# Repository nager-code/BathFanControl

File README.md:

# BathFanControl

**Feuchteabhängige Steuerung für einen Badlüfter.** Die Platine sitzt direkt im Lüfterkasten, misst die Luftfeuchte und schaltet den Lüfter nur so lange, wie das Lüften tatsächlich etwas bringt. Über WLAN lässt sie sich einstellen und aktualisieren.

> [!WARNING]
> **Stand V1.0: Planung abgeschlossen – noch nicht gebaut, nicht getestet.** Schaltplan und Platine sind in KiCad ohne Befund geprüft, es gibt aber noch kein gefertigtes Muster und noch keine Firmware. Siehe [Projektstand](doku/stand.md).

> [!CAUTION]
> **Netzspannung 230 V.** Die Schaltung führt Netzspannung und wird in einem Feuchtraum eingebaut. Betrieb nur im geschlossenen Gehäuse, Anschluss durch eine Elektrofachkraft. Mehr unter [Sicherheit](#sicherheit).

## Worum geht es?

Die alte Steuerung des Badlüfters lief teilweise acht Stunden am Stück, ohne dass die Feuchte sank. BathFanControl macht es besser:

- **Misst die Luftfeuchte** mit einem Sensirion SHT40 (mit Schutzmembran) direkt am Lüfter-Einlass.
- **Prüft den Fortschritt:** Sinkt die Feuchte beim Lüften nicht (z. B. weil die Außenluft selbst feucht ist), legt die Steuerung eine Pause ein, statt weiterzulaufen.
- **Erkennt Aktivität im Bad** über einen zweiten 230-V-Eingang vom Lichtschalter.
- **Ist über WLAN erreichbar** (ESP32-C3), z. B. für Home Assistant, Einstellungen und Updates.
- **Zeigt den Zustand** über eine RGB-LED im Gehäusedeckel.

Entwickelt für einen **KN2-UP-Unterputzlüfter** (Einrohr-Lüftungssystem, ca. 50 W). Andere Lüfter mit einem Schaltkanal bis zu dieser Leistung sollten ebenfalls passen, das ist aber nicht geprüft.

## Eckdaten

| | |
|---|---|
| Versorgung | 230 V AC, Netzteil Hi-Link HLK-PM03 (3,3 V, 1 A) |
| Eingänge | Lichtschalter (230 V, galvanisch getrennt über Optokoppler) |
| Ausgang | Lüfter, geschaltet über Optotriac und Triac (Phase) |
| Sensor | Sensirion SHT40-AD1F-R2, Temperatur und relative Feuchte |
| Controller | Espressif ESP32-C3-MINI-1 (WLAN, USB eingebaut) |
| Anschluss | 4-polige Schraubklemme: L, Licht, N, Lüfter |
| Programmieren | USB-C auf der Platine (nur ohne Netzspannung), danach per WLAN |
| Platine | 68 x 72,5 mm, 2 Lagen, nur von oben bestückt, alle Teile bei JLCPCB lieferbar |
| Gehäuse | 72,6 x 77,1 x 25,7 mm, 3D-Druck |
| Entwurfswerkzeuge | KiCad 10, OpenSCAD |

## Bilder

| Lageplan der Bauteile | Gehäuse geschlossen und offen |
|---|---|
|  |  |

Weitere Ansichten: [Platine von allen Seiten](doku/platine_3d_ansichten.png), [Einbaulage im Lüfterkasten](doku/einbaulage.svg), [3D-Modell zum Drehen](doku/platine_3d.glb) (glTF), [Schaltplan als PDF](doku/schaltplan.pdf).

## Nachbauen in fünf Schritten

1. **Verstehen:** [Funktion und Regellogik](doku/funktion.md) und [Schaltung](doku/schaltung.md) lesen.
2. **Prüfen:** die [Checkliste vor der Bestellung](doku/bestellen.md) abarbeiten.
3. **Bestellen:** Platine samt Bestückung mit dem [Bestellpaket](bestellpaket/LIESMICH.md) bei JLCPCB bestellen.
4. **Gehäuse drucken:** [Gehäuse](gehaeuse/README.md) aus flammhemmendem Material drucken.
5. **Aufbauen:** Firmware aufspielen, Platine lackieren, einbauen und anschließen lassen: [Aufbau und Einbau](doku/aufbau.md).

## Dokumentation

| Seite | Inhalt |
|---|---|
| [Funktion](doku/funktion.md) | Aufgabe, Lüfter, Regellogik der Firmware, WLAN |
| [Schaltung](doku/schaltung.md) | Funktionsblöcke, GPIO-Belegung, Bauteilauswahl, Datenblattprüfung |
| [Platine](doku/platine.md) | Eckdaten, Anordnung der Bauteile, Isolation, Leiterbahnen |
| [Bestellen](doku/bestellen.md) | Checkliste vor der Bestellung, Lagerbestand, Ausweichtypen |
| [Aufbau und Einbau](doku/aufbau.md) | Programmieren, Schutzlack, Anschluss, Montage |
| [Projektstand](doku/stand.md) | Was geprüft ist, was offen ist |
| [Gehäuse](gehaeuse/README.md) | 3D-Druck-Gehäuse: Aufbau, Dateien, offene Punkte |
| [Bestellpaket](bestellpaket/LIESMICH.md) | Fertigungsdaten für JLCPCB |
| [Skripte](skripte/README.md) | Platine und Bestellpaket neu erzeugen |

## Ordner

| Ordner | Inhalt |
|---|---|
| [`kicad/`](kicad) | KiCad-10-Projekt: Schaltplan, Platine, Designregeln, Projektbibliotheken |
| [`bestellpaket/`](bestellpaket) | Gerber, Bohrdaten, Stückliste und Bestückungsdatei im JLCPCB-Format |
| [`gehaeuse/`](gehaeuse) | Gehäuse: OpenSCAD-Modell, STL-Dateien, Bilder |
| [`doku/`](doku) | Dokumentation, Lageplan, Einbaulage, Schaltplan-PDF, Bilder, DRC-Bericht |
| [`skripte/`](skripte) | Skripte, die Platine und Bestellpaket neu erzeugen |

## Sicherheit

- Die Schaltung führt **Netzspannung**. Arbeiten nur im spannungsfreien Zustand.
- Betrieb nur im **geschlossenen Gehäuse**, außerhalb des Spritzbereichs.
- **Anschluss durch eine Elektrofachkraft** vornehmen bzw. abnehmen lassen.
- **USB nur anstecken, wenn die Platine vom Netz getrennt ist.**
- Bei Einrohrsystemen am gemeinsamen Schacht: **Brandschutzklappe nicht verändern.**
- Das Gehäuse ist ein Entwurf ohne Schutzart und ohne Normprüfung.

Nachbau und Betrieb auf eigene Verantwortung.

## Lizenz

© 2026 [nager-code](https://github.com/nager-code)

[CC BY-SA 4.0](LICENSE) – Weitergabe und Bearbeitung erlaubt, mit Namensnennung und unter gleichen Bedingungen.

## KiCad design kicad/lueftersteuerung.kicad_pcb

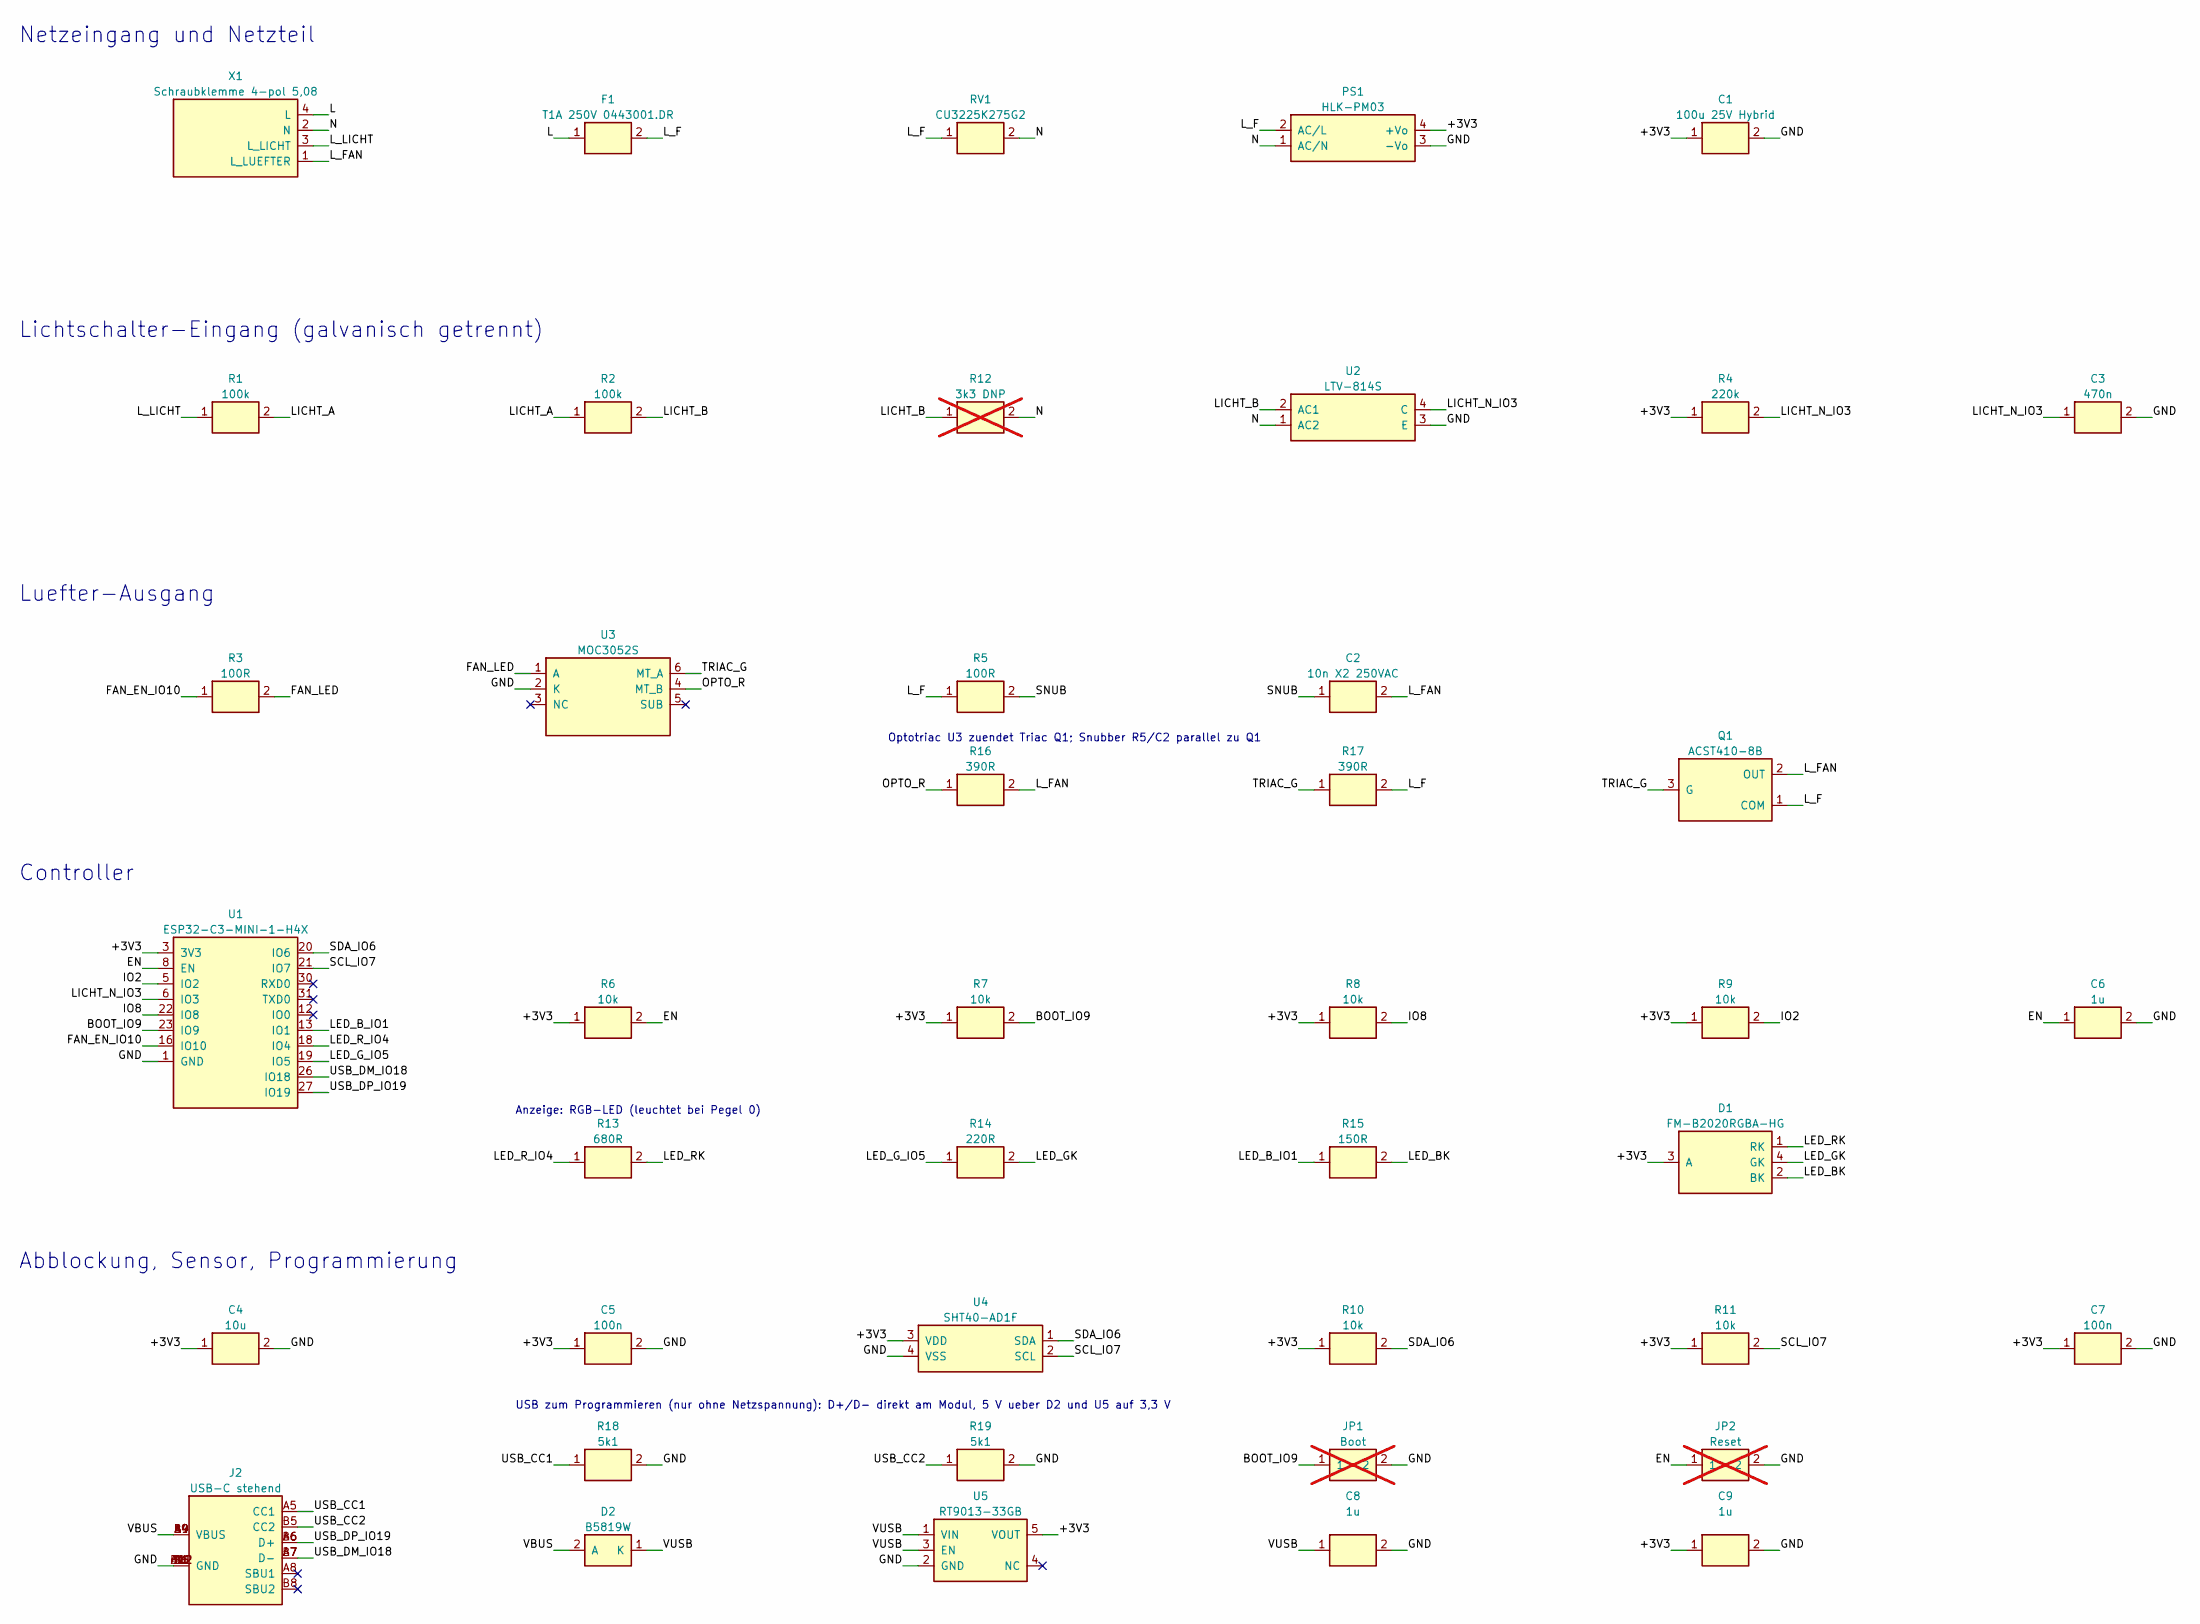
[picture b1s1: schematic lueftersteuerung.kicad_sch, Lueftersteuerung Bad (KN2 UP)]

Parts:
C1: 100u 25V Hybrid; CP_Elec_6.3x5.8
C2: 10n X2 250VAC; C_2220_Murata_GA355_X2
C3: 470n; C_0603_1608Metric
C4: 10u; C_0805_2012Metric
C5, C7: 100n; C_0603_1608Metric
C6, C8, C9: 1u; C_0603_1608Metric
D1: FM-B2020RGBA-HG; LED_RGB_NationStar_FM-B2020
D2: B5819W; D_SOD-123
F1: T1A 250V 0443001.DR; Fuse_SMD_10x3mm_Littelfuse443_UMT250
J2: USB-C stehend; USB_C_GCT_USB4145_stehend
JP1: Boot; SolderJumper-2_P1.3mm_Open_RoundedPad1.0x1.5mm; not fitted
JP2: Reset; SolderJumper-2_P1.3mm_Open_RoundedPad1.0x1.5mm; not fitted
PS1: HLK-PM03; Converter_ACDC_Hi-Link_HLK-PMxx
Q1: ACST410-8B; DPAK_ST_ACST4
R1, R2: 100k; R_1206_3216Metric
R3: 100R; R_0603_1608Metric
R4: 220k; R_0603_1608Metric
R5: 100R; R_1206_3216Metric
R6, R7, R8, R9, R10, R11: 10k; R_0603_1608Metric
R12: 3k3 DNP; R_0603_1608Metric; not fitted
R13: 680R; R_0603_1608Metric
R14: 220R; R_0603_1608Metric
R15: 150R; R_0603_1608Metric
R16: 390R; R_1206_3216Metric
R17: 390R; R_0603_1608Metric
R18, R19: 5k1; R_0603_1608Metric
RV1: CU3225K275G2; Varistor_TDK_CU3225
U1: ESP32-C3-MINI-1-H4X; ESP32-C3-MINI-1
U2: LTV-814S; LTV-814S_SMDIP-4_W9.53mm
U3: MOC3052S; MOC3052S_SMDIP-6_W9.53mm
U4: SHT40-AD1F; Sensirion_DFN-4_1.5x1.5mm_P0.8mm_SHT4x_NoCentralPad
U5: RT9013-33GB; SOT-23-5
X1: Schraubklemme 4-pol 5,08; Klemme_4pol_P5.08mm_Horizontal_THT

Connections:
/+3V3: C1.1, C4.1, C5.1, C7.1, C9.1, D1.3 (A), PS1.4 (+Vo), R4.1, R6.1, R7.1, R8.1, R9.1, R10.1, R11.1, U1.3 (3V3), U4.3 (VDD), U5.5 (VOUT)
/BOOT_IO9: JP1.1, R7.2, U1.23 (IO9)
/EN: C6.1, JP2.1, R6.2, U1.8 (EN)
/FAN_EN_IO10: R3.1, U1.16 (IO10)
/FAN_LED: R3.2, U3.1 (A)
/GND: C1.2, C3.2, C4.2, C5.2, C6.2, C7.2, C8.2, C9.2, J2.A1 (GND), J2.A12 (GND), J2.B1 (GND), J2.B12 (GND), J2.SH (GND), JP1.2, JP2.2, PS1.3 (-Vo), R18.2, R19.2, U1.1 (GND), U1.2 (GND), U1.11 (GND), U1.14 (GND), U1.36 (GND), U1.37 (GND), U1.38 (GND), U1.39 (GND), U1.40 (GND), U1.41 (GND), U1.42 (GND), U1.43 (GND), U1.44 (GND), U1.45 (GND), U1.46 (GND), U1.47 (GND), U1.48 (GND), U1.49 (GND), U1.50 (GND), U1.51 (GND), U1.52 (GND), U1.53 (GND), U2.3 (E), U3.2 (K), U4.4 (VSS), U5.2 (GND)
/IO2: R9.2, U1.5 (IO2)
/IO8: R8.2, U1.22 (IO8)
/L: F1.1, X1.4 (L)
/LED_BK: D1.2 (BK), R15.2
/LED_B_IO1: R15.1, U1.13 (IO1)
/LED_GK: D1.4 (GK), R14.2
/LED_G_IO5: R14.1, U1.19 (IO5)
/LED_RK: D1.1 (RK), R13.2
/LED_R_IO4: R13.1, U1.18 (IO4)
/LICHT_A: R1.2, R2.1
/LICHT_B: R2.2, R12.1, U2.2 (AC1)
/LICHT_N_IO3: C3.1, R4.2, U1.6 (IO3), U2.4 (C)
/L_F: F1.2, PS1.2 (AC/L), Q1.1 (COM), R5.1, R17.2, RV1.1
/L_FAN: C2.2, Q1.2 (OUT), R16.2, X1.1 (L_LUEFTER)
/L_LICHT: R1.1, X1.3 (L_LICHT)
/N: PS1.1 (AC/N), R12.2, RV1.2, U2.1 (AC2), X1.2 (N)
/OPTO_R: R16.1, U3.4 (MT_B)
/SCL_IO7: R11.2, U1.21 (IO7), U4.2 (SCL)
/SDA_IO6: R10.2, U1.20 (IO6), U4.1 (SDA)
/SNUB: C2.1, R5.2
/TRIAC_G: Q1.3 (G), R17.1, U3.6 (MT_A)
/USB_CC1: J2.A5 (CC1), R18.1
/USB_CC2: J2.B5 (CC2), R19.1
/USB_DM_IO18: J2.A7 (D-), J2.B7 (D-), U1.26 (IO18)
/USB_DP_IO19: J2.A6 (D+), J2.B6 (D+), U1.27 (IO19)
/VBUS: D2.2 (A), J2.A4 (VBUS), J2.A9 (VBUS), J2.B4 (VBUS), J2.B9 (VBUS)
/VUSB: C8.1, D2.1 (K), U5.1 (VIN), U5.3 (EN)

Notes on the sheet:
Abblockung, Sensor, Programmierung
Controller
Lichtschalter-Eingang (galvanisch getrennt)
Luefter-Ausgang
USB zum Programmieren (nur ohne Netzspannung): D+/D- direkt am Modul, 5 V ueber D2 und U5 auf 3,3 V
Netzeingang und Netzteil
Anzeige: RGB-LED (leuchtet bei Pegel 0)
Optotriac U3 zuendet Triac Q1; Snubber R5/C2 parallel zu Q1

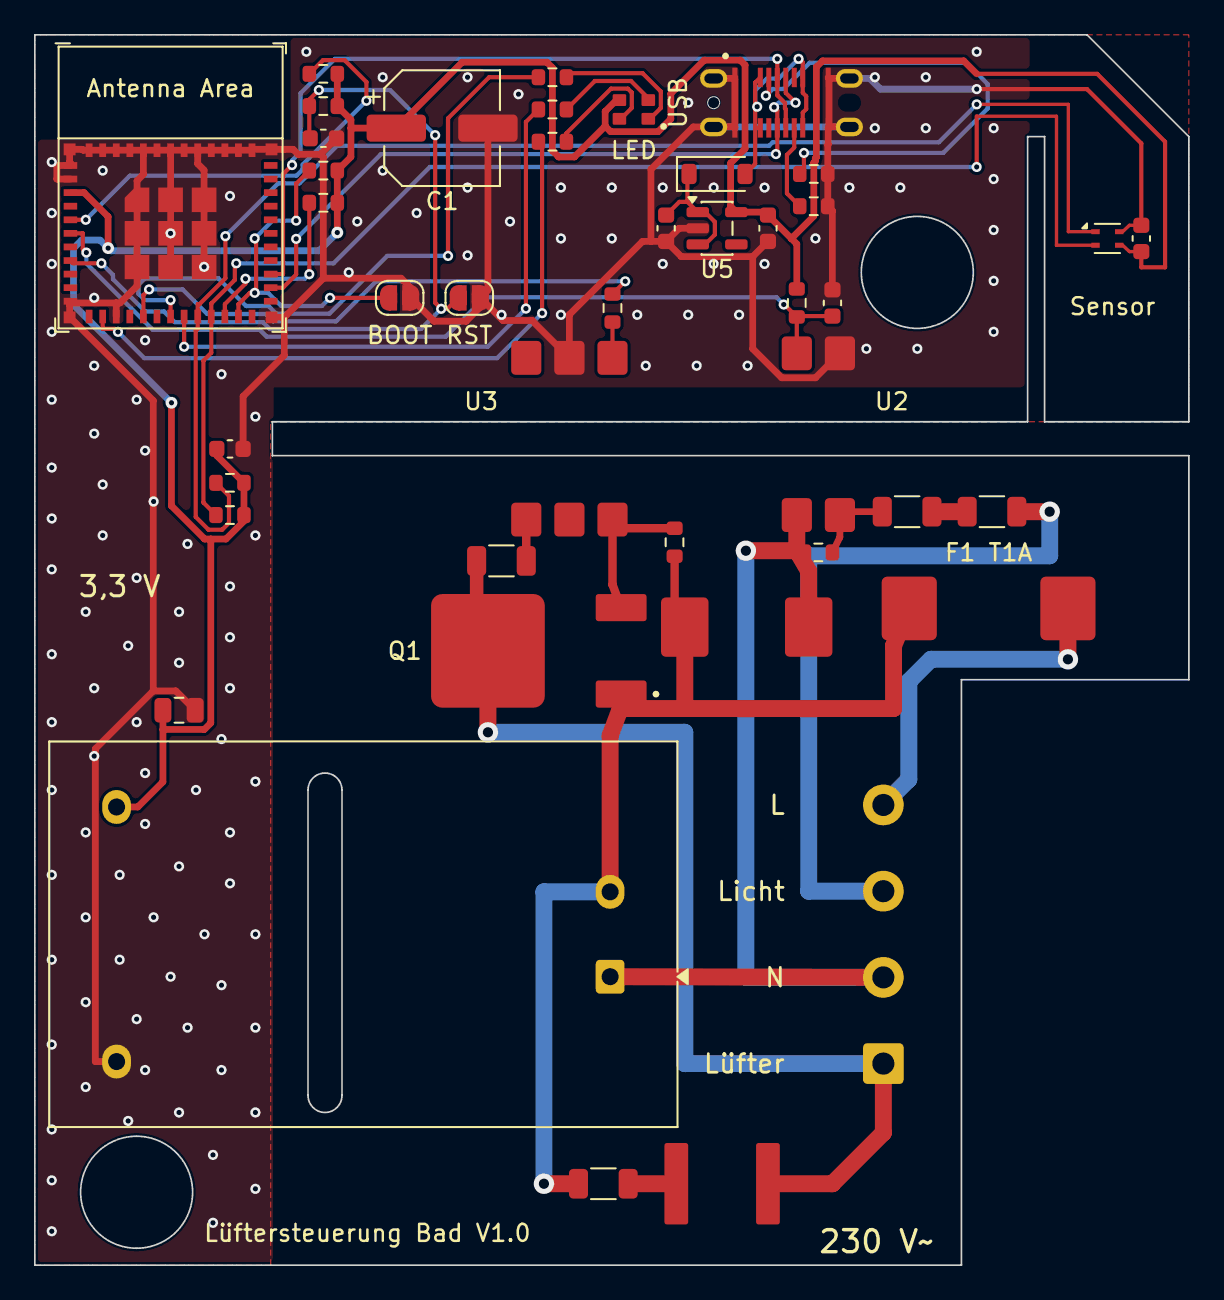
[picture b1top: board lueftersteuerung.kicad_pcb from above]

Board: 2 copper layers, 68.0 x 72.5 mm, 43 parts (0 on the bottom side), 33 nets.

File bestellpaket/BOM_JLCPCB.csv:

Comment,Designator,Footprint,LCSC Part #,Manufacturer Part,Quantity,Note
"100u 25V Hybrid-Polymer-Elko SMD 6,3x5,8",C1,CP_Elec_6.3x5.8,C454668,Panasonic EEHZK1E101UP,1,"JLCPCB Extended; fuer feuchte Waerme spezifiziert (85 C / 85-90 % r. F., 2000 h, AEC-Q200). Beim Lackieren die Gummidichtung am Boden nicht ganz verschliessen, Lack halogenfrei"
10n X2 250VAC 2220,C2,C_2220_Murata_GA355_X2,C237426,Murata GA355QR7GB103KW01L,1,JLCPCB Extended; Sicherheitskondensator Klasse X2
470n 25V X7R 0603,C3,C_0603_1608Metric,C1623,CL10B474KA8NNNC,1,JLCPCB Basic
10u 25V X5R 0805,C4,C_0805_2012Metric,C15850,CL21A106KAYNNNE,1,JLCPCB Basic
100n 50V X7R 0603,"C5,C7",C_0603_1608Metric,C14663,CC0603KRX7R9BB104,2,JLCPCB Basic
1u 50V X5R 0603,"C6,C8,C9",C_0603_1608Metric,C15849,CL10A105KB8NNNC,3,JLCPCB Basic
RGB-LED 2020 gemeinsame Anode,D1,LED_RGB_NationStar_FM-B2020,C42421005,Foshan NationStar FM-B2020RGBA-HG,1,"JLCPCB Extended; Drehlage in der JLC-Vorschau pruefen (Eckmarke = Pin 1 = rot, unten rechts)"
Schottky-Diode 1 A 40 V SOD-123,D2,D_SOD-123,C8598,B5819W,1,JLCPCB Basic; Rueckstromschutz zur USB-Buchse
Sicherung T1A 250VAC SMD 10x3,F1,Fuse_SMD_10x3mm_Littelfuse443_UMT250,C95352,Littelfuse 0443001.DR,1,JLCPCB Extended; alternativ Schurter UMT 250 1A T (3403.0166.11)
"USB-C-Buchse stehend, 16-polig, 7,5 mm hoch, Zapfen 2,3 mm",J2,USB_C_GCT_USB4145_stehend,C5291559,GCT USB4145-03-0230-C,1,"JLCPCB Extended; die vier Gehaeusezapfen gehen durch die Platine und werden unten verloetet. Gleiches Loetbild mit kuerzeren Zapfen: USB4145-03-0170-C (C5181332), -0070-C (C5815189)"
"Netzteil 230V -> 3,3V 1A, bedrahtet",PS1,Converter_ACDC_Hi-Link_HLK-PMxx,C209904,Hi-Link HLK-PM03,1,"JLCPCB Extended, bedrahtet (Wellenloeten); Ausweichtyp mit fast gleichem Stiftbild: YLPTEC HAW3-220S03T2 (C19724490), vor dem Tausch Masse pruefen"
"ACST410-8B Triac 800V 4A DPAK, ueberspannungsfest",Q1,DPAK_ST_ACST4,C221462,STMicroelectronics ACST410-8BTR,1,JLCPCB Extended; IGT max. 10 mA
100k 1% 1206 200V,"R1,R2",R_1206_3216Metric,C17900,1206W4F1003T5E,2,JLCPCB Basic
100R 1% 0603,R3,R_0603_1608Metric,C22775,0603WAF1000T5E,1,JLCPCB Basic
220k 1% 0603,R4,R_0603_1608Metric,C22961,0603WAF2203T5E,1,JLCPCB Basic
100R 1% 1206,R5,R_1206_3216Metric,C17901,1206W4F1000T5E,1,JLCPCB Basic; impulsfest waere Panasonic ERJ-P08F1000V (C4195341)
10k 1% 0603,"R6,R7,R8,R9,R10,R11",R_0603_1608Metric,C25804,0603WAF1002T5E,6,JLCPCB Basic
680R 1% 0603,R13,R_0603_1608Metric,C23228,0603WAF6800T5E,1,JLCPCB Basic; LED rot
220R 1% 0603,R14,R_0603_1608Metric,C22962,0603WAF2200T5E,1,JLCPCB Basic; LED gruen
150R 1% 0603,R15,R_0603_1608Metric,C22808,0603WAF1500T5E,1,JLCPCB Basic; LED blau
390R 1% 1206,R16,R_1206_3216Metric,C4491,1206W4F3900T5E,1,"JLCPCB Extended; Zuendwiderstand, Bauform 1206 wegen der Impulsspannung"
390R 1% 0603,R17,R_0603_1608Metric,C23151,0603WAF3900T5E,1,JLCPCB Basic; Gate nach COM
5k1 1% 0603,R18,R_0603_1608Metric,C23186,0603WAF5101T5E,1,JLCPCB Basic; USB CC1
5k1 1% 0603,R19,R_0603_1608Metric,C23186,0603WAF5101T5E,1,JLCPCB Basic; USB CC2
Varistor 275VAC SMD,RV1,Varistor_TDK_CU3225,C211106,TDK CU3225K275G2 (B72650M0271K072),1,"JLCPCB Extended; Bauform 8,0 x 6,3 mm"
ESP32-C3-MINI-1-H4X,U1,ESP32-C3-MINI-1,C41349510,Espressif ESP32-C3-MINI-1-H4X,1,JLCPCB Extended; N4 (C2838502) ist abgekuendigt (NRND)
LTV-814S AC-Optokoppler,U2,LTV-814S_SMDIP-4_W9.53mm,C125118,Lite-On LTV-814S-TA1,1,JLCPCB Extended
"MOC3052S Optotriac 600V, ohne Nullspannungsschalter",U3,MOC3052S_SMDIP-6_W9.53mm,C115471,Lite-On MOC3052S-TA1,1,"JLCPCB Extended; zuendet Q1. IFT max. 10 mA, 5 kV Isolation (UL, VDE)"
SHT40 Feuchte/Temperatur mit Membran,U4,Sensirion_DFN-4_1.5x1.5mm_P0.8mm_SHT4x_NoCentralPad,C7461846,Sensirion SHT40-AD1F-R2,1,JLCPCB Extended; mit Polyimid-Membran (Endung F). Nicht die Fremdmarke C54823945 nehmen. Nicht ueberlackieren
"Spannungsregler 3,3 V 500 mA SOT-23-5",U5,SOT-23-5,C47773,Richtek RT9013-33GB,1,JLCPCB Extended; versorgt die Platine beim Programmieren aus USB
"Schraubklemme 4-polig 5,08 mm, bedrahtet",X1,Klemme_4pol_P5.08mm_Horizontal_THT,C5443561,"Phoenix Contact MKDS 1,5/4-5,08 (1715747)",1,"JLCPCB Extended, bedrahtet (Wellenloeten); 250 V / 17,5 A, 0,14-1,5 mm2"

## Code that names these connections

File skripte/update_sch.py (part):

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blk=t[s:e].replace('"Value" "IRM-02-3.3"','"Value" "%s"'%PS1_VAL)
t=t[:s]+blk+t[e:]
# 1b) Klemme X1: die Pins liegen bei Leitereinfuehrung nach rechts von unten nach oben 1..4.
#     Gewuenschte Reihenfolge von oben: L, Licht, N, Luefter -> L = 4, L_LICHT = 3, N = 2, L_LUEFTER = 1
i=t.find('(symbol "Luefter:KLEMME_4"'); j=t.find('\n    (symbol "Luefter:',i+5)
blk=t[i:j]
for name,old,new_ in (("L","1","4"),("L_LUEFTER","4","1")):
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# 2) Luefterstufe: statt des Photo-Triacs AQH3223A ein Optotriac MOC3052S (U3), der den Triac ACST410-8B (Q1) zuendet.
#    MOC3052S laut Datenblatt: 1 = Anode, 2 = Kathode, 3 = nicht belegt, 4 und 6 = Ausgang, 5 = Substrat (nicht anschliessen).
#    Das Symbol des AQH3223A wird dazu umnummeriert; der Ausgang geht nicht mehr an L_F / L_FAN, sondern an
#    TRIAC_G (Pin 6, Gate von Q1) und OPTO_R (Pin 4, ueber R16 an L_FAN). Q1, R16 und R17 kommen in Schritt 6 dazu.
i=t.find('(symbol "Luefter:AQH3223A"'); j=t.find('\n    (symbol "Luefter:',i+5)
if j<0: j=t.find('\n  )',i)
PINMAP = {("A","2"):("A","1"), ("K","3"):("K","2"), ("NC","1"):("NC","3"), ("NC","4"):None,
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t=t[:s]+blk+t[e:]
t=sub1(r'  \(no_connect \(at 99\.06 140\.97\) \(uuid "[^"]+"\)\)\n','',t)
# Die beiden Ausgangspins sind gleichwertig; fuer ein kreuzungsfreies Layout geht Pin 6 ans Gate und Pin 4 an R16.
t=sub1(re.escape('(label "L_FAN" (at 127.00 133.35 0)'),'(label "TRIAC_G" (at 127.00 133.35 0)',t)
t=sub1(re.escape('(label "L_F" (at 127.00 135.89 0)'),'(label "OPTO_R" (at 127.00 135.89 0)',t)
# 2b) LTV-814: die beiden AC-Eingangspins sind gleichwertig; getauscht, damit das Layout ohne Kreuzung auskommt
i=t.find('(symbol "Luefter:LTV-814S"'); j=t.find('\n    (symbol "Luefter:',i+5)
if j<0: j=t.find('\n  )',i)
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# R17 leitet Leckstrom am Gate ab. Q1: COM an L_F (hinter der Sicherung), OUT an L_FAN (zur Klemme).
YT_ = 152.40
neu_el += inst("R", "R16", "390R", "Resistor_SMD:R_1206_3216Metric", 172.72, YT_, ("1", "2"))
neu_el += wire(166.37, YT_, 163.83, YT_, "r16a") + label("OPTO_R", 163.83, YT_, True, "r16a")
neu_el += wire(179.07, YT_, 181.61, YT_, "r16b") + label("L_FAN", 181.61, YT_, False, "r16b")
neu_el += inst("R", "R17", "390R", "Resistor_SMD:R_0603_1608Metric", 233.68, YT_, ("1", "2"))
neu_el += wire(227.33, YT_, 224.79, YT_, "r17a") + label("TRIAC_G", 224.79, YT_, True, "r17a")
neu_el += wire(240.03, YT_, 242.57, YT_, "r17b") + label("L_F", 242.57, YT_, False, "r17b")
neu_el += inst("ACST", "Q1", "ACST410-8B", "lueftersteuerung:DPAK_ST_ACST4", 294.64, YT_, ("3", "2", "1"))
neu_el += wire(284.48, YT_, 281.94, YT_, "q1g") + label("TRIAC_G", 281.94, YT_, True, "q1g")
neu_el += wire(304.80, YT_ - 2.54, 307.34, YT_ - 2.54, "q1o") + label("L_FAN", 307.34, YT_ - 2.54, False, "q1o")
neu_el += wire(304.80, YT_ + 2.54, 307.34, YT_ + 2.54, "q1c") + label("L_F", 307.34, YT_ + 2.54, False, "q1c")
neu_el += ('  (text "Optotriac U3 zuendet Triac Q1; Snubber R5/C2 parallel zu Q1" (exclude_from_sim no) (at 157.48 144.78 0) '
           '(effects (font (size 1.27 1.27)) (justify left bottom)) (uuid "%s"))\n' % uid("text2"))
neu_el += ('  (text "Anzeige: RGB-LED (leuchtet bei Pegel 0)" (exclude_from_sim no) (at 96.52 205.74 0) '
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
